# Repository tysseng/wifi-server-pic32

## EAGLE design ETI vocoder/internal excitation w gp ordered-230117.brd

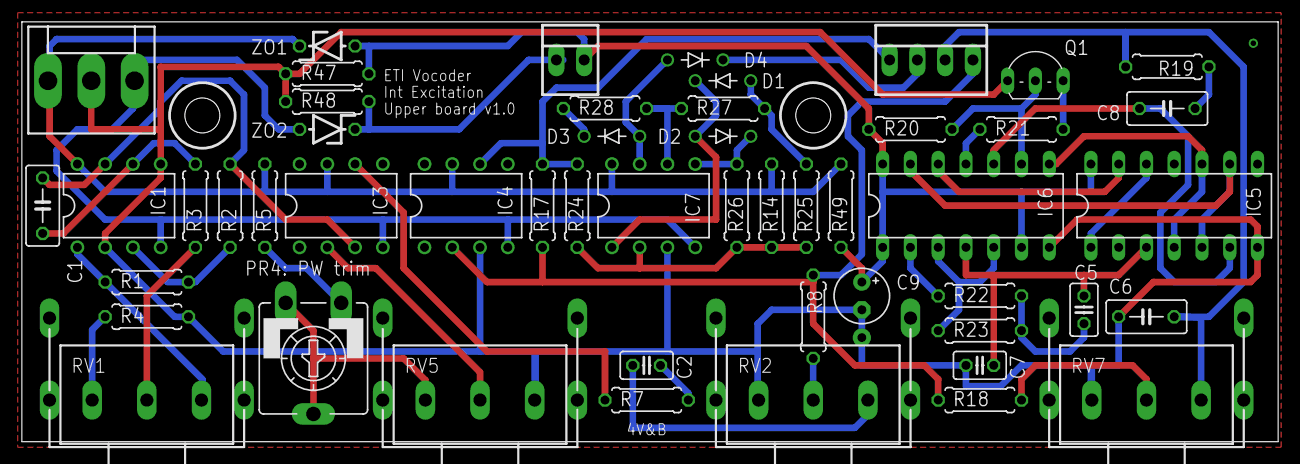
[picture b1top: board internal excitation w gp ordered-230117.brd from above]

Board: 2 copper layers, 114.9 x 38.4 mm, 51 parts (0 on the bottom side), 43 nets.

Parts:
BOARD1: 22-23-2041
BOARD1-PWR: 22-23-2021
C1: 100n; C050-030X075
C2: 10n; C025-025X050
C5: 220p; C025-025X050
C6: 33n; C050-030X075
C7: 100p; C025-025X050
C8: 10n; C050-030X075
C9: 10u; E2,5-5
D1, D2, D3, D4: 1N4148; DO35-5J
IC1, IC7: LM1458N; DIL08
IC3: TL081P; DIL08
IC4: UA741P; DIL08
IC5: 4006N; DIL14
IC6: 4030N; DIL14
POWER: KK-156-3
PR4: 2k2; CA9V
Q1: BC182L; TO92-ECB
R1: 10k; 0207/7
R2: 5k6; 0207/7
R3: 18k; 0207/7
R4: 560R; 0207/7
R5: 11k; 0207/7
R7: 150k; 0207/7
R8, R18: 47k; 0207/7
R14: 1M; 0207/7
R17: 100k; 0207/7
R19: 15k; 0207/7
R20, R24, R25, R26, R27, R28: 4k7; 0207/7
R21: 22k; 0207/7
R22: 330k; 0207/7
R23: 27k; 0207/7
R47, R48: 1k; 0207/7
R49: 3k3; 0207/7
RV1, RV2: 10k log; POT16_W_BRACKET
RV5, RV7: 10k; POT16_W_BRACKET
ZO1, ZO2: 5V1; ZDIO-5

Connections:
1_12: IC5.1, IC5.12
4_10: IC5.4, IC5.10, IC6.8
5_9: IC5.5, IC5.9, IC6.13
+12V: IC1.8, IC3.7, IC4.7, IC7.8, POWER.1, R5.1, R14.2, R49.2, ZO1.C
-12V: IC1.4, IC3.4, IC4.4, IC7.4, POWER.3, ZO2.A
BOARD2_MIX: BOARD1.4, IC4.2, R8.1, R17.2, R18.1
GND: C6.2, C7.2, C9.-, IC1.2, IC1.5, IC4.3, IC5.7, IC6.7, IC7.3, POWER.2, Q1.E, R4.2, R47.1, R48.2, RV2.1A, RV5.1E, RV7.1A
unnamed: IC1.3, R1.1, R2.1
unnamed: IC1.1, R1.2, RV1.1E
unnamed: R3.2, RV1.1S
unnamed: C1.1, IC1.6, R3.1
unnamed: R4.1, RV1.1A
unnamed: C1.2, IC1.7, IC3.3, R2.2
unnamed: IC3.2, RV5.1S
unnamed: PR4.A, R5.2
unnamed: PR4.E, PR4.S, RV5.1A
unnamed: IC3.6, R7.2
unnamed: C2.2, R7.1
unnamed: C2.1, RV2.1E
unnamed: R8.2, RV2.1S
unnamed: IC6.3, IC6.5, R23.1
unnamed: D1.C, D2.A, IC7.1
unnamed: IC7.2, R14.1, R24.1, R25.2, R26.2
unnamed: D2.C, IC7.5, R26.1
unnamed: D1.A, R25.1, R27.2
unnamed: IC7.6, R27.1, R28.2
unnamed: D3.C, R28.1
unnamed: D3.A, D4.A, IC7.7
unnamed: R18.2, RV7.1S
unnamed: C8.1, R19.2
unnamed: C8.2, IC5.6, IC6.10
unnamed: IC6.9, Q1.C, R20.1
unnamed: IC6.11, R21.1
unnamed: IC6.2, R22.1
unnamed: C5.2, R22.2, R23.2
unnamed: IC5.13, IC6.12
unnamed: C5.1, C7.1, IC5.3, IC6.4
unnamed: Q1.B, R21.2
VCA_CTRL: BOARD1.2, D4.C
VCA_SIGNAL: BOARD1.3, C6.1, R19.1, RV7.1E
VDD: BOARD1-PWR.2, C9.+, IC5.14, IC6.1, IC6.6, IC6.14, R20.2, R47.2, R49.1, ZO1.A
VSS: BOARD1-PWR.1, R48.1, ZO2.C
X: BOARD1.1, IC4.6, R17.1, R24.2

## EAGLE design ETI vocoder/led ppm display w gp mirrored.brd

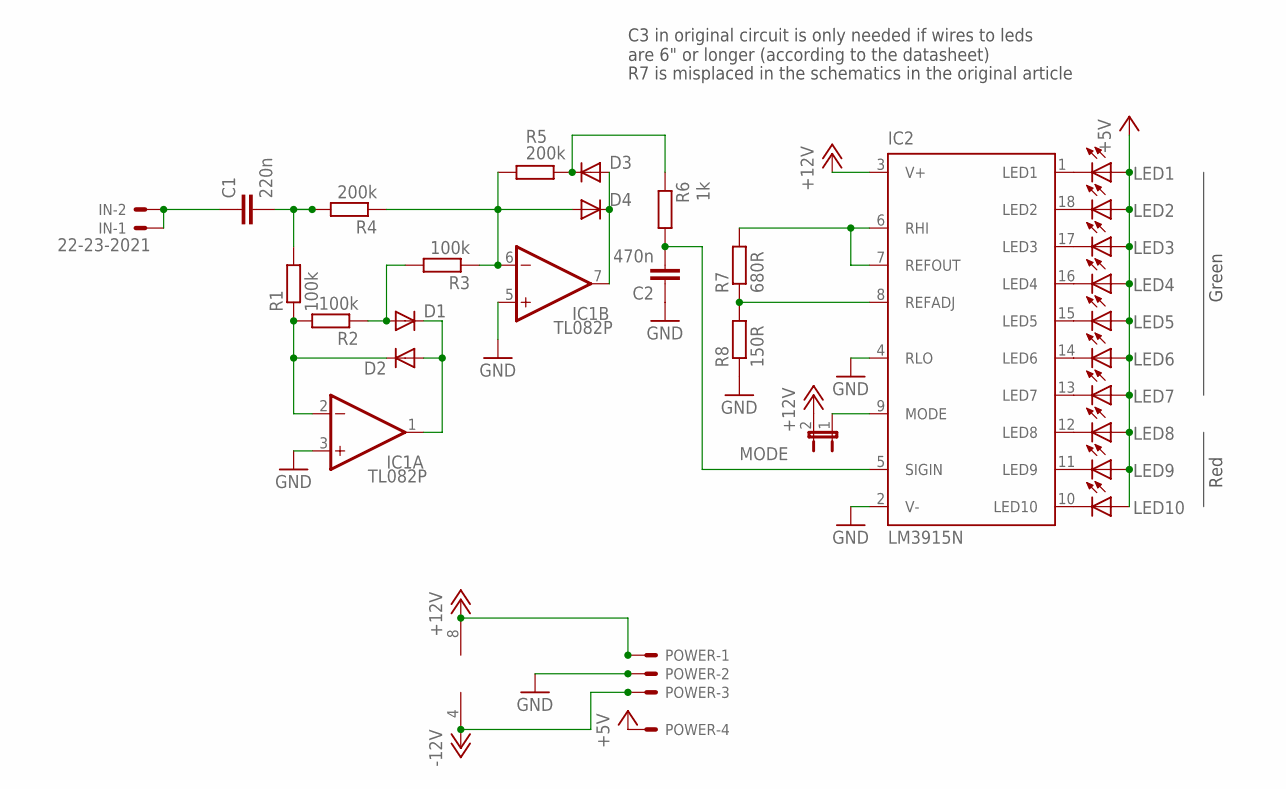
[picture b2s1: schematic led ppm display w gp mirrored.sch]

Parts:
C1: 220n; C050-025X075
C2: 470n; C050-025X075
D1, D2, D3, D4: 1N4148DOJ35-5; DO35-5J
IC1: TL082P; DIL08
IC2: LM3915N; DIL18
IN: 22-23-2021
LED1, LED2, LED3, LED4, LED5, LED6, LED7, LED8, LED9, LED10: LED3MM
MODE: JP1E; JP1
POWER: KK-156-4
R1, R2, R3: 100k; 0207/7
R4, R5: 200k; 0207/7
R6: 1k; 0207/7
R7: 680R; 0207/7
R8: 150R; 0207/7

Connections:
+5V: LED1.A, LED2.A, LED3.A, LED4.A, LED5.A, LED6.A, LED7.A, LED8.A, LED9.A, LED10.A, POWER.4
+12V: IC1.8 (V+), IC2.3 (V+), MODE.2, POWER.1
-12V: IC1.4 (V-), POWER.3
GND: C2.1, IC1.3 (+IN), IC1.5 (+IN), IC2.2 (V-), IC2.4 (RLO), POWER.2, R8.1
MODE: IC2.9 (MODE), MODE.1
unnamed: D1.A, R2.1, R3.2
unnamed: D2.C, IC1.2 (-IN), R1.1, R2.2
unnamed: D1.C, D2.A, IC1.1 (OUT)
unnamed: D4.A, IC1.6 (-IN), R3.1, R4.1, R5.2
unnamed: D3.C, R5.1, R6.1
unnamed: C1.2, R1.2, R4.2
unnamed: D3.A, D4.C, IC1.7 (OUT)
unnamed: C2.2, IC2.5 (SIGIN), R6.2
unnamed: IC2.6 (RHI), IC2.7 (REFOUT), R7.2
unnamed: IC2.1 (LED1), LED1.K (C)
unnamed: IC2.18 (LED2), LED2.K (C)
unnamed: IC2.17 (LED3), LED3.K (C)
unnamed: IC2.16 (LED4), LED4.K (C)
unnamed: IC2.15 (LED5), LED5.K (C)
unnamed: IC2.14 (LED6), LED6.K (C)
unnamed: IC2.13 (LED7), LED7.K (C)
unnamed: IC2.12 (LED8), LED8.K (C)
unnamed: IC2.11 (LED9), LED9.K (C)
unnamed: IC2.10 (LED10), LED10.K (C)
unnamed: IC2.8 (REFADJ), R7.1, R8.2
unnamed: C1.1, IN.1, IN.2

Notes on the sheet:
C3 in original circuit is only needed if wires to leds are 6" or longer (according to the datasheet)
Red
Green
R7 is misplaced in the schematics in the original article

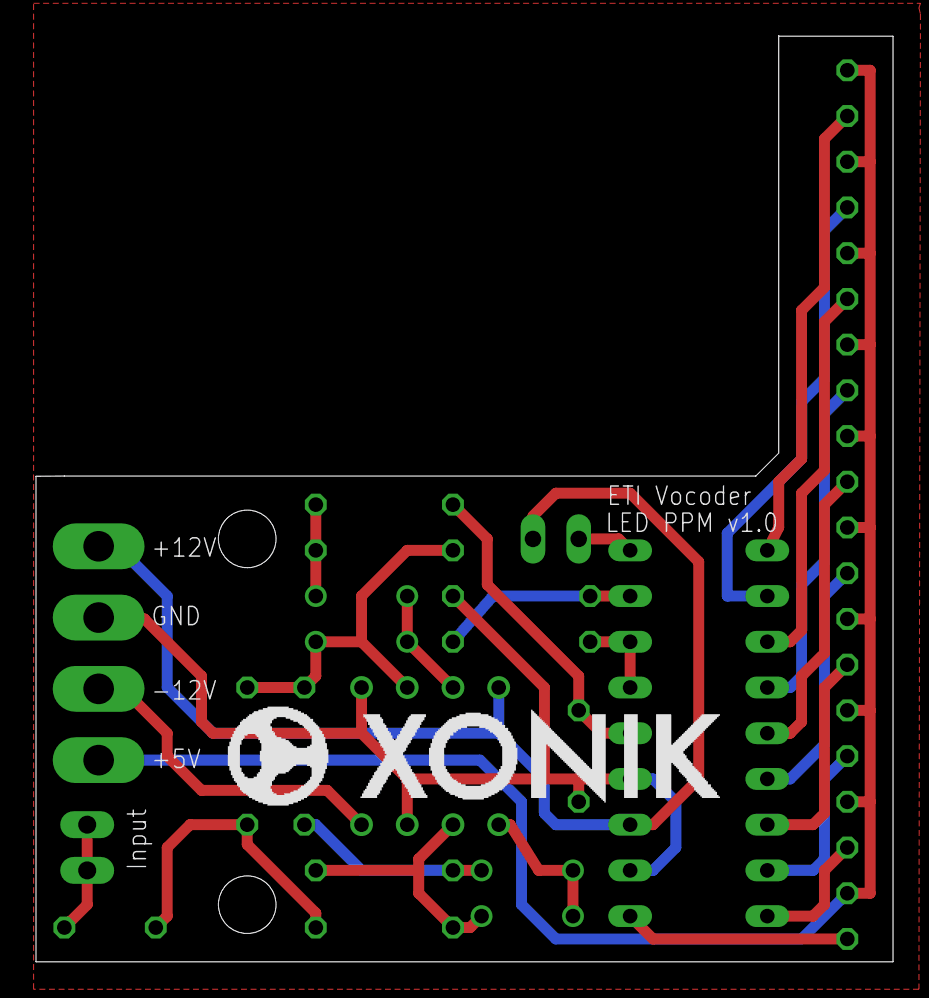
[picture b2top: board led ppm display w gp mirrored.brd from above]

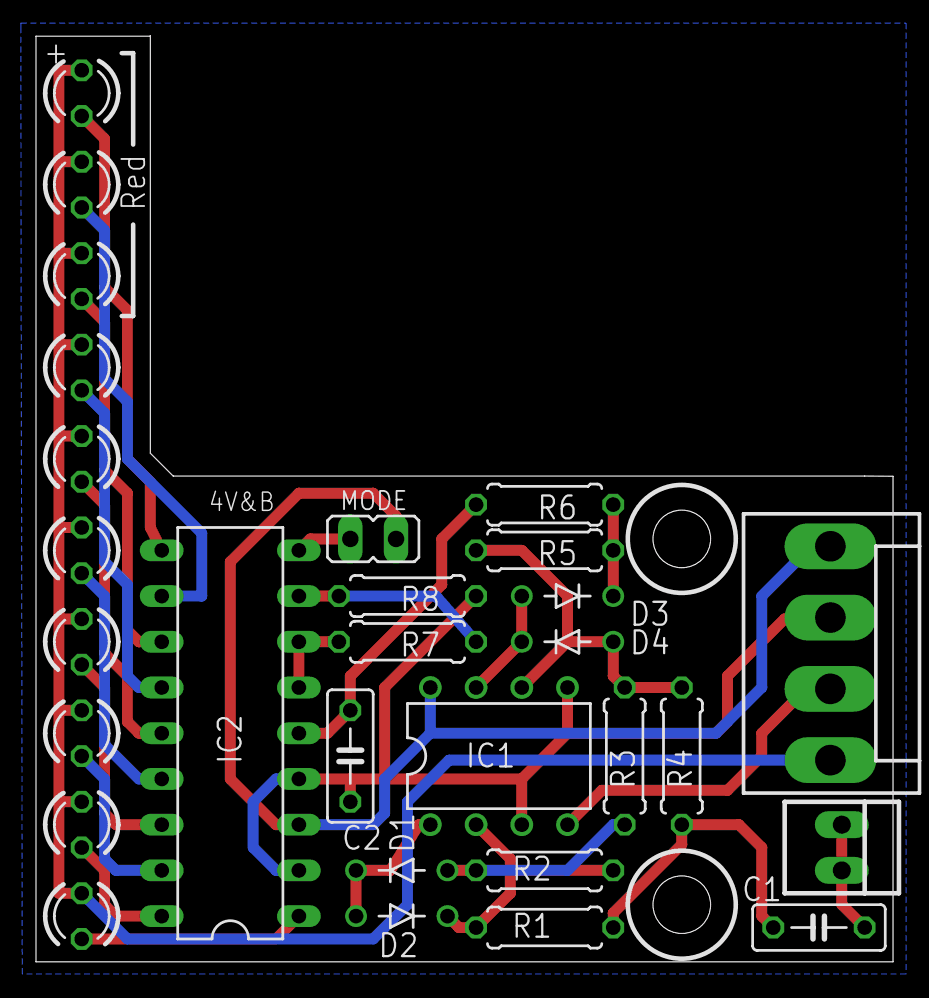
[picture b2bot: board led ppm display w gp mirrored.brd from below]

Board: 2 copper layers, 47.6 x 51.4 mm, 29 parts (29 on the bottom side), 26 nets.

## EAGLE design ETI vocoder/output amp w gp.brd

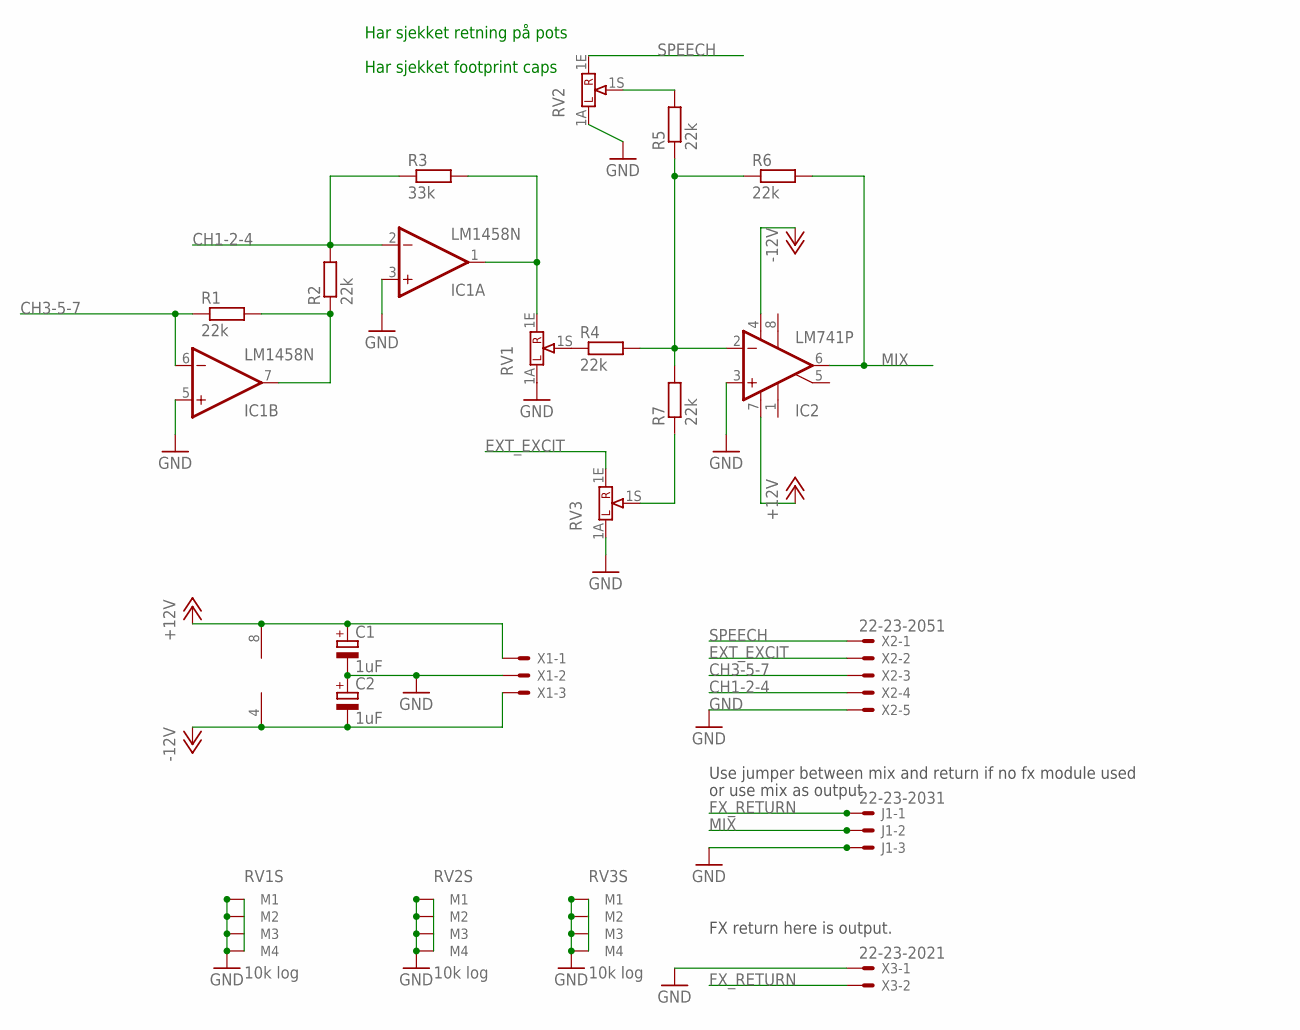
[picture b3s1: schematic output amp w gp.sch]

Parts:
C1, C2: 1uF; E2,5-5
IC1: LM1458N; DIL08
IC2: LM741P; DIL08
J1: 22-23-2031
R1, R2, R4, R5, R6, R7: 22k; 0207/7
R3: 33k; 0207/7
RV1, RV2, RV3: 10k log; POT16_W_BRACKET
X1: KK-156-3
X2: 22-23-2051
X3: 22-23-2021

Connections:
+12V: C1.+, IC1.8 (V+), IC2.7 (V+), X1.1
-12V: C2.-, IC1.4 (V-), IC2.4 (V-), X1.3
CH1-2-4: IC1.2 (-IN), R2.2, R3.1, X2.4
CH3-5-7: IC1.6 (-IN), R1.1, X2.3
EXT_EXCIT: RV3.1E, X2.2
FX_RETURN: J1.1, X3.2
GND: C1.-, C2.+, IC1.3 (+IN), IC1.5 (+IN), IC2.3 (+IN), J1.3, RV1.1A, RV1.M1, RV1.M2, RV1.M3, RV1.M4, RV2.1A, RV2.M1, RV2.M2, RV2.M3, RV2.M4, RV3.1A, RV3.M1, RV3.M2, RV3.M3, RV3.M4, X1.2, X2.5, X3.1
MIX: IC2.6 (OUT), J1.2, R6.2
unnamed: R4.1, RV1.1S
unnamed: IC1.7 (OUT), R1.2, R2.1
unnamed: IC1.1 (OUT), R3.2, RV1.1E
unnamed: R7.1, RV3.1S
unnamed: IC2.2 (-IN), R4.2, R5.1, R6.1, R7.2
unnamed: R5.2, RV2.1S
SPEECH: RV2.1E, X2.1

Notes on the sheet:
Use jumper between mix and return if no fx module used
Har sjekket retning på pots
FX return here is output.
or use mix as output
Har sjekket footprint caps

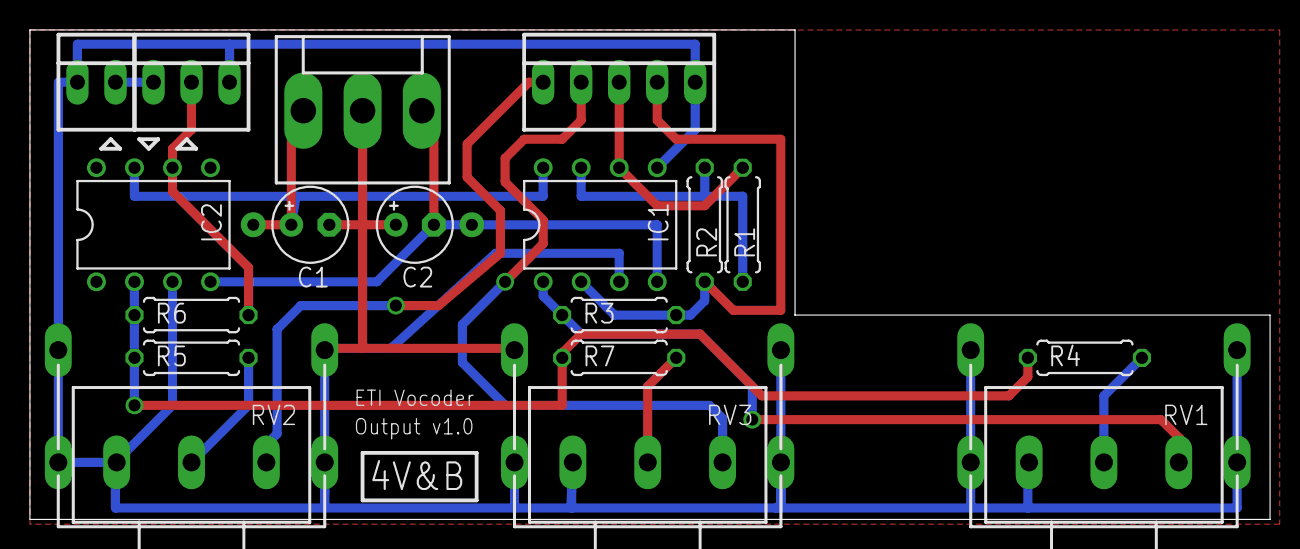
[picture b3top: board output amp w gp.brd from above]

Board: 2 copper layers, 82.9 x 32.7 mm, 18 parts (0 on the bottom side), 15 nets.
